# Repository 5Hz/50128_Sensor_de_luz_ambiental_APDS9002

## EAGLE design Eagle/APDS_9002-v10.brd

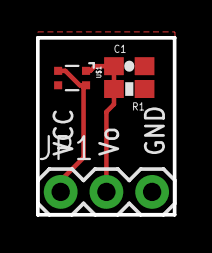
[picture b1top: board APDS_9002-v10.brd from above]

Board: 2 copper layers, 7.6 x 9.8 mm, 5 parts (1 on the bottom side), 3 nets.

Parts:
C1: 10uF; 0603-CAP
JP1: 1X03
LOGO1: LOGO_5HZ_CIRC_4MM; 5HZ_LOGO_CIRC_4MM
R1: 1K; 0603-RES
U$1: APDS-9002

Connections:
GND: C1.2, JP1.3, R1.1
unnamed: C1.1, JP1.2, R1.2, U$1.IOUT
VCC: JP1.1, U$1.VCC1, U$1.VCC2

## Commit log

2014-01-14 creación

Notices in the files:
parts and their libraries:
SparkFun: Licensing: CC v3.0 Share-Alike You are welcome to use this library for commercial purposes.
